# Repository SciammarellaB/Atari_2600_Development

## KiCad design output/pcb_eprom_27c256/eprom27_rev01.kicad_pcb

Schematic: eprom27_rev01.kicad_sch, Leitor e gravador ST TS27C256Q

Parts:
C1, C2, C3, C4, C5: 100nF 25V; C_Disc_D5.0mm_W2.5mm_P2.50mm
J1: ENDERECOS - MEGA; PinHeader_1x16_P2.54mm_Vertical
J2: LEITURA +5M - MEGA; PinHeader_1x10_P2.54mm_Vertical
J3: ESCRITA E CONTROLES - MEGA; PinHeader_1x12_P2.54mm_Vertical
J4: FONTES EXTERNAS; TerminalBlock_Phoenix_MKDS-1,5-6-5.08_1x06_P5.08mm_Horizont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
Q1, Q2, Q3, Q4, Q5, Q6, Q7, Q8, Q9, Q10: 2N7000 Microchip TO92 S-G-D; TO-92_Inline_Wide
R1, R2, R3, R4, R5, R6, R7, R8, R33, R36: 220R; R_Axial_DIN0207_L6.3mm_D2.5mm_P7.62mm_Horizontal
R9, R10, R11, R12, R13, R14, R15, R16, R34, R37: 100k; R_Axial_DIN0207_L6.3mm_D2.5mm_P7.62mm_Horizontal
R17, R18, R19, R20, R21, R22, R23, R24, R35, R38: 10k; R_Axial_DIN0207_L6.3mm_D2.5mm_P7.62mm_Horizontal
R25, R26, R27, R28, R29, R30, R31, R32: 4k7; R_Axial_DIN0207_L6.3mm_D2.5mm_P7.62mm_Horizontal
R39: 22k 1%; R_Axial_DIN0207_L6.3mm_D2.5mm_P7.62mm_Horizontal
R40: 10k 1%; R_Axial_DIN0207_L6.3mm_D2.5mm_P7.62mm_Horizontal
TP1: GND; TestPoint_THTPad_D2.0mm_Drill1.0mm
TP2: +5M; TestPoint_THTPad_D2.0mm_Drill1.0mm
TP3: VCC_EP; TestPoint_THTPad_D2.0mm_Drill1.0mm
TP4: VPP; TestPoint_THTPad_D2.0mm_Drill1.0mm
TP5: V_AUX; TestPoint_THTPad_D2.0mm_Drill1.0mm
TP6: VREF; TestPoint_THTPad_D2.0mm_Drill1.0mm
TP7: CE_N; TestPoint_THTPad_D2.0mm_Drill1.0mm
TP8: OE_N; TestPoint_THTPad_D2.0mm_Drill1.0mm
U1: ST TS27C256Q / DIP28; DIP-28_W15.24mm_LongPads
U2, U3: LM339N / DIP14; DIP-14_W7.62mm_LongPads

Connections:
+5M: J2.9 (+5M), R25.1 (+5M), R26.1 (+5M), R27.1 (+5M), R28.1 (+5M), R29.1 (+5M), R30.1 (+5M), R31.1 (+5M), R32.1 (+5M), R39.1 (+5M), TP2.1
A0: J1.1 (A0), U1.10 (A0)
A1: J1.2 (A1), U1.9 (A1)
A2: J1.3 (A2), U1.8 (A2)
A3: J1.4 (A3), U1.7 (A3)
A4: J1.5 (A4), U1.6 (A4)
A5: J1.6 (A5), U1.5 (A5)
A6: J1.7 (A6), U1.4 (A6)
A7: J1.8 (A7), U1.3 (A7)
A8: J1.9 (A8), U1.25 (A8)
A9: J1.10 (A9), U1.24 (A9)
A10: J1.11 (A10), U1.21 (A10)
A11: J1.12 (A11), U1.23 (A11)
A12: J1.13 (A12), U1.2 (A12)
A13: J1.14 (A13), U1.26 (A13)
A14: J1.15 (A14), U1.27 (A14)
CE_DRV: J3.9 (CE_DRV), R33.1 (CE_DRV)
CE_N: Q9.3 (CE_N), R35.2 (CE_N), TP7.1, U1.20 (CE_N)
G0: Q1.2 (G0), R1.2 (G0), R9.1 (G0)
G1: Q2.2 (G1), R2.2 (G1), R10.1 (G1)
G2: Q3.2 (G2), R3.2 (G2), R11.1 (G2)
G3: Q4.2 (G3), R4.2 (G3), R12.1 (G3)
G4: Q5.2 (G4), R5.2 (G4), R13.1 (G4)
G5: Q6.2 (G5), R6.2 (G5), R14.1 (G5)
G6: Q7.2 (G6), R7.2 (G6), R15.1 (G6)
G7: Q8.2 (G7), R8.2 (G7), R16.1 (G7)
G9: Q9.2 (G9), R33.2 (G9), R34.1 (G9)
G10: Q10.2 (G10), R36.2 (G10), R37.1 (G10)
GND: C1.2 (GND), C2.2 (GND), C3.2 (GND), C4.2 (GND), C5.2 (GND), J1.16 (GND), J2.10 (GND), J3.11 (GND), J4.2 (GND), J4.4 (GND), J4.6 (GND), Q1.1 (GND), Q2.1 (GND), Q3.1 (GND), Q4.1 (GND), Q5.1 (GND), Q6.1 (GND), Q7.1 (GND), Q8.1 (GND), Q9.1 (GND), Q10.1 (GND), R9.2 (GND), R10.2 (GND), R11.2 (GND), R12.2 (GND), R13.2 (GND), R14.2 (GND), R15.2 (GND), R16.2 (GND), R34.2 (GND), R37.2 (GND), R40.2 (GND), TP1.1, U1.14 (GND), U2.12 (GND), U3.12 (GND)
OE_DRV: J3.10 (OE_DRV), R36.1 (OE_DRV)
OE_N: Q10.3 (OE_N), R38.2 (OE_N), TP8.1, U1.22 (OE_N)
Q0: Q1.3 (Q0), R17.2 (Q0), U1.11 (Q0), U2.5 (Q0)
Q1: Q2.3 (Q1), R18.2 (Q1), U1.12 (Q1), U2.7 (Q1)
Q2: Q3.3 (Q2), R19.2 (Q2), U1.13 (Q2), U2.9 (Q2)
Q3: Q4.3 (Q3), R20.2 (Q3), U1.15 (Q3), U2.11 (Q3)
Q4: Q5.3 (Q4), R21.2 (Q4), U1.16 (Q4), U3.5 (Q4)
Q5: Q6.3 (Q5), R22.2 (Q5), U1.17 (Q5), U3.7 (Q5)
Q6: Q7.3 (Q6), R23.2 (Q6), U1.18 (Q6), U3.9 (Q6)
Q7: Q8.3 (Q7), R24.2 (Q7), U1.19 (Q7), U3.11 (Q7)
RD0: J2.1 (RD0), R25.2 (RD0), U2.2 (RD0)
RD1: J2.2 (RD1), R26.2 (RD1), U2.1 (RD1)
RD2: J2.3 (RD2), R27.2 (RD2), U2.14 (RD2)
RD3: J2.4 (RD3), R28.2 (RD3), U2.13 (RD3)
RD4: J2.5 (RD4), R29.2 (RD4), U3.2 (RD4)
RD5: J2.6 (RD5), R30.2 (RD5), U3.1 (RD5)
RD6: J2.7 (RD6), R31.2 (RD6), U3.14 (RD6)
RD7: J2.8 (RD7), R32.2 (RD7), U3.13 (RD7)
VCC_EP: C1.1 (VCC_EP), J4.1 (VCC_EP), R17.1 (VCC_EP), R18.1 (VCC_EP), R19.1 (VCC_EP), R20.1 (VCC_EP), R21.1 (VCC_EP), R22.1 (VCC_EP), R23.1 (VCC_EP), R24.1 (VCC_EP), R35.1 (VCC_EP), R38.1 (VCC_EP), TP3.1, U1.28 (VCC_EP)
VPP: C2.1 (VPP), J4.3 (VPP), TP4.1, U1.1 (VPP)
VREF: C5.1 (VREF), R39.2 (VREF), R40.1 (VREF), TP6.1, U2.4 (VREF), U2.6 (VREF), U2.8 (VREF), U2.10 (VREF), U3.4 (VREF), U3.6 (VREF), U3.8 (VREF), U3.10 (VREF)
V_AUX: C3.1 (V_AUX), C4.1 (V_AUX), J4.5 (V_AUX), TP5.1, U2.3 (V_AUX), U3.3 (V_AUX)
WR0: J3.1 (WR0), R1.1 (WR0)
WR1: J3.2 (WR1), R2.1 (WR1)
WR2: J3.3 (WR2), R3.1 (WR2)
WR3: J3.4 (WR3), R4.1 (WR3)
WR4: J3.5 (WR4), R5.1 (WR4)
WR5: J3.6 (WR5), R6.1 (WR5)
WR6: J3.7 (WR6), R7.1 (WR6)
WR7: J3.8 (WR7), R8.1 (WR7)

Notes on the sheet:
REVISAO 0.1 / PROTOTIPO - SEM PROTECAO CONTRA INVERSAO - FONTES EXTERNAS MANUAIS

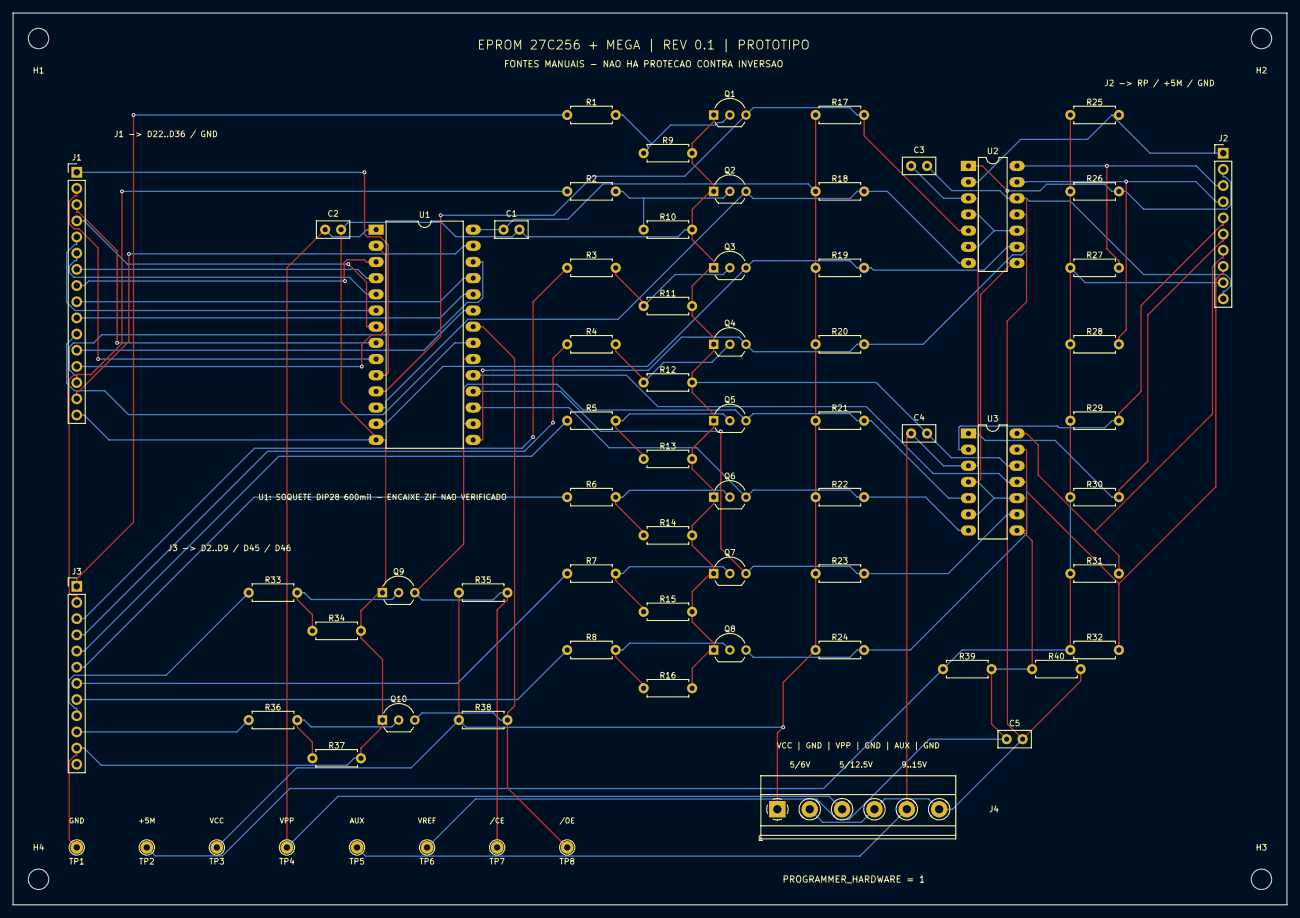
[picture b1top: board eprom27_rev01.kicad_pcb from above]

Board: 2 copper layers, 200.0 x 140.0 mm, 74 parts (0 on the bottom side), 59 nets.

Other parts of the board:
H1, H2, H3, H4: M3 NPTH; MountingHole_3.2mm_M3

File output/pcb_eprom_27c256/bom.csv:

Referencia,Valor,Tipo,Biblioteca,Footprint
U1,ST TS27C256Q / DIP28,dip28,Package_DIP,DIP-28_W15.24mm_LongPads
U2,LM339N / DIP14,dip14,Package_DIP,DIP-14_W7.62mm_LongPads
U3,LM339N / DIP14,dip14,Package_DIP,DIP-14_W7.62mm_LongPads
J1,ENDERECOS - MEGA,header16,Connector_PinHeader_2.54mm,PinHeader_1x16_P2.54mm_Vertical
J2,LEITURA +5M - MEGA,header10,Connector_PinHeader_2.54mm,PinHeader_1x10_P2.54mm_Vertical
J3,ESCRITA E CONTROLES - MEGA,header12,Connector_PinHeader_2.54mm,PinHeader_1x12_P2.54mm_Vertical
J4,FONTES EXTERNAS,terminal6,TerminalBlock_Phoenix,"TerminalBlock_Phoenix_MKDS-1,5-6-5.08_1x06_P5.08mm_Horizontal"
Q1,2N7000 Microchip TO92 S-G-D,mos,Package_TO_SOT_THT,TO-92_Inline_Wide
R1,220R,res,Resistor_THT,R_Axial_DIN0207_L6.3mm_D2.5mm_P7.62mm_Horizontal
R9,100k,res,Resistor_THT,R_Axial_DIN0207_L6.3mm_D2.5mm_P7.62mm_Horizontal
R17,10k,res,Resistor_THT,R_Axial_DIN0207_L6.3mm_D2.5mm_P7.62mm_Horizontal
R25,4k7,res,Resistor_THT,R_Axial_DIN0207_L6.3mm_D2.5mm_P7.62mm_Horizontal
Q2,2N7000 Microchip TO92 S-G-D,mos,Package_TO_SOT_THT,TO-92_Inline_Wide
R2,220R,res,Resistor_THT,R_Axial_DIN0207_L6.3mm_D2.5mm_P7.62mm_Horizontal
R10,100k,res,Resistor_THT,R_Axial_DIN0207_L6.3mm_D2.5mm_P7.62mm_Horizontal
R18,10k,res,Resistor_THT,R_Axial_DIN0207_L6.3mm_D2.5mm_P7.62mm_Horizontal
R26,4k7,res,Resistor_THT,R_Axial_DIN0207_L6.3mm_D2.5mm_P7.62mm_Horizontal
Q3,2N7000 Microchip TO92 S-G-D,mos,Package_TO_SOT_THT,TO-92_Inline_Wide
R3,220R,res,Resistor_THT,R_Axial_DIN0207_L6.3mm_D2.5mm_P7.62mm_Horizontal
R11,100k,res,Resistor_THT,R_Axial_DIN0207_L6.3mm_D2.5mm_P7.62mm_Horizontal
R19,10k,res,Resistor_THT,R_Axial_DIN0207_L6.3mm_D2.5mm_P7.62mm_Horizontal
R27,4k7,res,Resistor_THT,R_Axial_DIN0207_L6.3mm_D2.5mm_P7.62mm_Horizontal
Q4,2N7000 Microchip TO92 S-G-D,mos,Package_TO_SOT_THT,TO-92_Inline_Wide
R4,220R,res,Resistor_THT,R_Axial_DIN0207_L6.3mm_D2.5mm_P7.62mm_Horizontal
R12,100k,res,Resistor_THT,R_Axial_DIN0207_L6.3mm_D2.5mm_P7.62mm_Horizontal
R20,10k,res,Resistor_THT,R_Axial_DIN0207_L6.3mm_D2.5mm_P7.62mm_Horizontal
R28,4k7,res,Resistor_THT,R_Axial_DIN0207_L6.3mm_D2.5mm_P7.62mm_Horizontal
Q5,2N7000 Microchip TO92 S-G-D,mos,Package_TO_SOT_THT,TO-92_Inline_Wide
R5,220R,res,Resistor_THT,R_Axial_DIN0207_L6.3mm_D2.5mm_P7.62mm_Horizontal
R13,100k,res,Resistor_THT,R_Axial_DIN0207_L6.3mm_D2.5mm_P7.62mm_Horizontal
R21,10k,res,Resistor_THT,R_Axial_DIN0207_L6.3mm_D2.5mm_P7.62mm_Horizontal
R29,4k7,res,Resistor_THT,R_Axial_DIN0207_L6.3mm_D2.5mm_P7.62mm_Horizontal
Q6,2N7000 Microchip TO92 S-G-D,mos,Package_TO_SOT_THT,TO-92_Inline_Wide
R6,220R,res,Resistor_THT,R_Axial_DIN0207_L6.3mm_D2.5mm_P7.62mm_Horizontal
R14,100k,res,Resistor_THT,R_Axial_DIN0207_L6.3mm_D2.5mm_P7.62mm_Horizontal
R22,10k,res,Resistor_THT,R_Axial_DIN0207_L6.3mm_D2.5mm_P7.62mm_Horizontal
R30,4k7,res,Resistor_THT,R_Axial_DIN0207_L6.3mm_D2.5mm_P7.62mm_Horizontal
Q7,2N7000 Microchip TO92 S-G-D,mos,Package_TO_SOT_THT,TO-92_Inline_Wide
R7,220R,res,Resistor_THT,R_Axial_DIN0207_L6.3mm_D2.5mm_P7.62mm_Horizontal
R15,100k,res,Resistor_THT,R_Axial_DIN0207_L6.3mm_D2.5mm_P7.62mm_Horizontal
R23,10k,res,Resistor_THT,R_Axial_DIN0207_L6.3mm_D2.5mm_P7.62mm_Horizontal
R31,4k7,res,Resistor_THT,R_Axial_DIN0207_L6.3mm_D2.5mm_P7.62mm_Horizontal
Q8,2N7000 Microchip TO92 S-G-D,mos,Package_TO_SOT_THT,TO-92_Inline_Wide
R8,220R,res,Resistor_THT,R_Axial_DIN0207_L6.3mm_D2.5mm_P7.62mm_Horizontal
R16,100k,res,Resistor_THT,R_Axial_DIN0207_L6.3mm_D2.5mm_P7.62mm_Horizontal
R24,10k,res,Resistor_THT,R_Axial_DIN0207_L6.3mm_D2.5mm_P7.62mm_Horizontal
R32,4k7,res,Resistor_THT,R_Axial_DIN0207_L6.3mm_D2.5mm_P7.62mm_Horizontal
Q9,2N7000 Microchip TO92 S-G-D,mos,Package_TO_SOT_THT,TO-92_Inline_Wide
R33,220R,res,Resistor_THT,R_Axial_DIN0207_L6.3mm_D2.5mm_P7.62mm_Horizontal
R34,100k,res,Resistor_THT,R_Axial_DIN0207_L6.3mm_D2.5mm_P7.62mm_Horizontal
R35,10k,res,Resistor_THT,R_Axial_DIN0207_L6.3mm_D2.5mm_P7.62mm_Horizontal
Q10,2N7000 Microchip TO92 S-G-D,mos,Package_TO_SOT_THT,TO-92_Inline_Wide
R36,220R,res,Resistor_THT,R_Axial_DIN0207_L6.3mm_D2.5mm_P7.62mm_Horizontal
R37,100k,res,Resistor_THT,R_Axial_DIN0207_L6.3mm_D2.5mm_P7.62mm_Horizontal
R38,10k,res,Resistor_THT,R_Axial_DIN0207_L6.3mm_D2.5mm_P7.62mm_Horizontal
R39,22k 1%,res,Resistor_THT,R_Axial_DIN0207_L6.3mm_D2.5mm_P7.62mm_Horizontal
R40,10k 1%,res,Resistor_THT,R_Axial_DIN0207_L6.3mm_D2.5mm_P7.62mm_Horizontal
C1,100nF 25V,cap,Capacitor_THT,C_Disc_D5.0mm_W2.5mm_P2.50mm
C2,100nF 25V,cap,Capacitor_THT,C_Disc_D5.0mm_W2.5mm_P2.50mm
C3,100nF 25V,cap,Capacitor_THT,C_Disc_D5.0mm_W2.5mm_P2.50mm
C4,100nF 25V,cap,Capacitor_THT,C_Disc_D5.0mm_W2.5mm_P2.50mm
C5,100nF 25V,cap,Capacitor_THT,C_Disc_D5.0mm_W2.5mm_P2.50mm
TP1,GND,test,TestPoint,TestPoint_THTPad_D2.0mm_Drill1.0mm
TP2,+5M,test,TestPoint,TestPoint_THTPad_D2.0mm_Drill1.0mm
TP3,VCC_EP,test,TestPoint,TestPoint_THTPad_D2.0mm_Drill1.0mm
TP4,VPP,test,TestPoint,TestPoint_THTPad_D2.0mm_Drill1.0mm
TP5,V_AUX,test,TestPoint,TestPoint_THTPad_D2.0mm_Drill1.0mm
TP6,VREF,test,TestPoint,TestPoint_THTPad_D2.0mm_Drill1.0mm
TP7,CE_N,test,TestPoint,TestPoint_THTPad_D2.0mm_Drill1.0mm
TP8,OE_N,test,TestPoint,TestPoint_THTPad_D2.0mm_Drill1.0mm
H1,M3 NPTH,hole,MountingHole,MountingHole_3.2mm_M3
H2,M3 NPTH,hole,MountingHole,MountingHole_3.2mm_M3
H3,M3 NPTH,hole,MountingHole,MountingHole_3.2mm_M3
H4,M3 NPTH,hole,MountingHole,MountingHole_3.2mm_M3
